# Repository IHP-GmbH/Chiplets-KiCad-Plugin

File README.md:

# Chiplets-KiCad-Plugin

KiCad (pcbnew) plugins for the IHP heterogeneous-integration ecosystem. This
repository hosts every current and future KiCad plugin built for chiplet and
interposer design on IHP SG13G2, so they share one license, one CI setup and
one place to look. Each plugin is self-contained under `plugins/<name>/` and is
installed independently.

Both plugins are alpha: `chiplet_export` lists what it does not verify in its
README's Status section, and `resizer_passive_elements` is a proof of concept.

## Plugins

| Plugin | What it does |
|--------|--------------|
| [`plugins/chiplet_export`](plugins/chiplet_export/README.md) | pcbnew action plugin that drives the HYP -> GDS -> canonical `.chiplet` pipeline in one click. Produces the canonical `.chiplet`, the interposer GDS, the driving Hyperlynx `.hyp`, and optionally a complete-assembly GDS. The same pipeline runs headless as `chiplet-export` ([reference](plugins/chiplet_export/CLI.md)). Consumed by adk-tools as a submodule. |
| [`plugins/resizer_passive_elements`](plugins/resizer_passive_elements/README.md) | pcbnew action plugin that resizes placed passive devices on the board. Today it covers `cap_cmim`: it regenerates each instance's footprint through the OpenIntM4TM2 `cmim_footprint_gen.py` from the `w`/`l` or `Capacitance` fields, then swaps it in preserving placement, nets and the technology fields the export flow reads. |

## Layout

```
Chiplets-KiCad-Plugin/
├── plugins/
│   ├── chiplet_export/       one self-contained pcbnew plugin (Python package)
│   │   ├── __init__.py       registers the ActionPlugin with pcbnew
│   │   ├── ...               action, dialog, pipeline/, writers/, tests/
│   │   ├── requirements.txt  that plugin's worker venv deps
│   │   └── README.md         that plugin's docs
│   └── resizer_passive_elements/   same shape, one plugin per directory
├── docs/                     pages adk-docs includes; docs/reference/ is generated
├── scripts/                  write_cli_help.py writes docs/reference/
├── .github/workflows/        CI, one matrix entry per plugin
├── pyproject.toml            test configuration for every plugin's suite
├── conftest.py               sibling checkouts for those suites
├── LICENSE                   GPL-3.0-or-later, applies repo-wide
└── README.md                 this file
```

Each plugin directory is a Python package in its own right: its `__init__.py`
registers the pcbnew action and its modules use relative imports, so the
package name is whatever the directory is called (`chiplet_export`). Nothing at
the repository root is a Python package; the root only carries shared metadata.

## Installing a plugin

Symlink (recommended for development) or copy the specific plugin directory,
not the whole repository, into KiCad's scripting plugins folder. For
`chiplet_export` on Linux with KiCad 9.0:

```bash
ln -s /path/to/Chiplets-KiCad-Plugin/plugins/chiplet_export \
      ~/.config/kicad/9.0/scripting/plugins/chiplet_export
```

Then follow that plugin's own README for its worker venv and dependencies
(`plugins/chiplet_export/README.md`).

## Adding a new plugin

1. Create `plugins/<new_name>/` with its own `__init__.py`, an `ActionPlugin`
   subclass that registers on import, a `README.md`, and a `tests/` suite. Use
   relative imports inside the package so it is loadable under `<new_name>`.
2. If it ships tests, give it a `requirements.txt`, add its requirements to
   the root `pyproject.toml` dependencies and its `tests` directory to
   `testpaths` there, and add `<new_name>` to the `matrix.plugin` list in
   `.github/workflows/tests.yml`. Every suite runs from the repository root
   under the one pytest configuration in `pyproject.toml`.
3. Keep the plugin self-contained: shared code, if it ever appears, is a
   separate decision, not an implicit dependency between plugin directories.

## License

GPL-3.0-or-later for the repository. See `LICENSE`. Individual plugins may
vendor code under compatible licenses and note it in their own README (for
example `chiplet_export` vendors a GPL-2.0-or-later Hyperlynx writer derived
from KiCad, redistributed under the "or later" clause).

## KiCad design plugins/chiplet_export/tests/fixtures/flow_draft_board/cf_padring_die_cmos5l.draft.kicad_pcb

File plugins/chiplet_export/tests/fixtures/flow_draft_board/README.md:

# flow_draft_board

One draft-path pair, the board and the sheet of the same run, for the
padring_die_cmos5l example: interposer_pnr's bumps, pdn, route, export and
schematic stages, with the interposer-pnr and gds_to_kicad that pair the draft
sheet with the draft board, run fresh in an ADK-Tools image on 2026-11-01 from
the elaborate outputs of the example's run of 2026-10-31. Route 38/38 nets with 0 DRC; `kicad-cli pcb drc
--schematic-parity` on the pair reports 0 issues.

`cf_padring_die_cmos5l.draft.kicad_pcb` is the draft board export wrote: three
die footprints (U1 to U3, `chiplet_dies:<top cell>`) and 32 wire-bond carrier
pads from `chiplet_carrier`, each with IO_PAD_ID its own Reference and linked
to no sheet symbol. It has no board-root property, and its `.kicad_pro` is not
kept here. Unchanged from the run; it names no host path. sha256:
`9eca915a4bbdaace4148dacd2968bab7d51490bd6b63304e09e3800e974fcc59`.

`cf_padring_die_cmos5l.draft.kicad_sch` is the system sheet the same run drew
(chiplet_to_kicad_sch), unchanged. Its title-block comment 1 holds the digest
of the run's `design.chiplet`. sha256:
`0bbf948c7161b148b46a9ad07959d492071d2ef00eebd769e3398ec668fddf8f`.

`test_board_save.py` saves copies of both the way a GUI save does;
`test_io_pad_ids.py` reads the board's carriers.

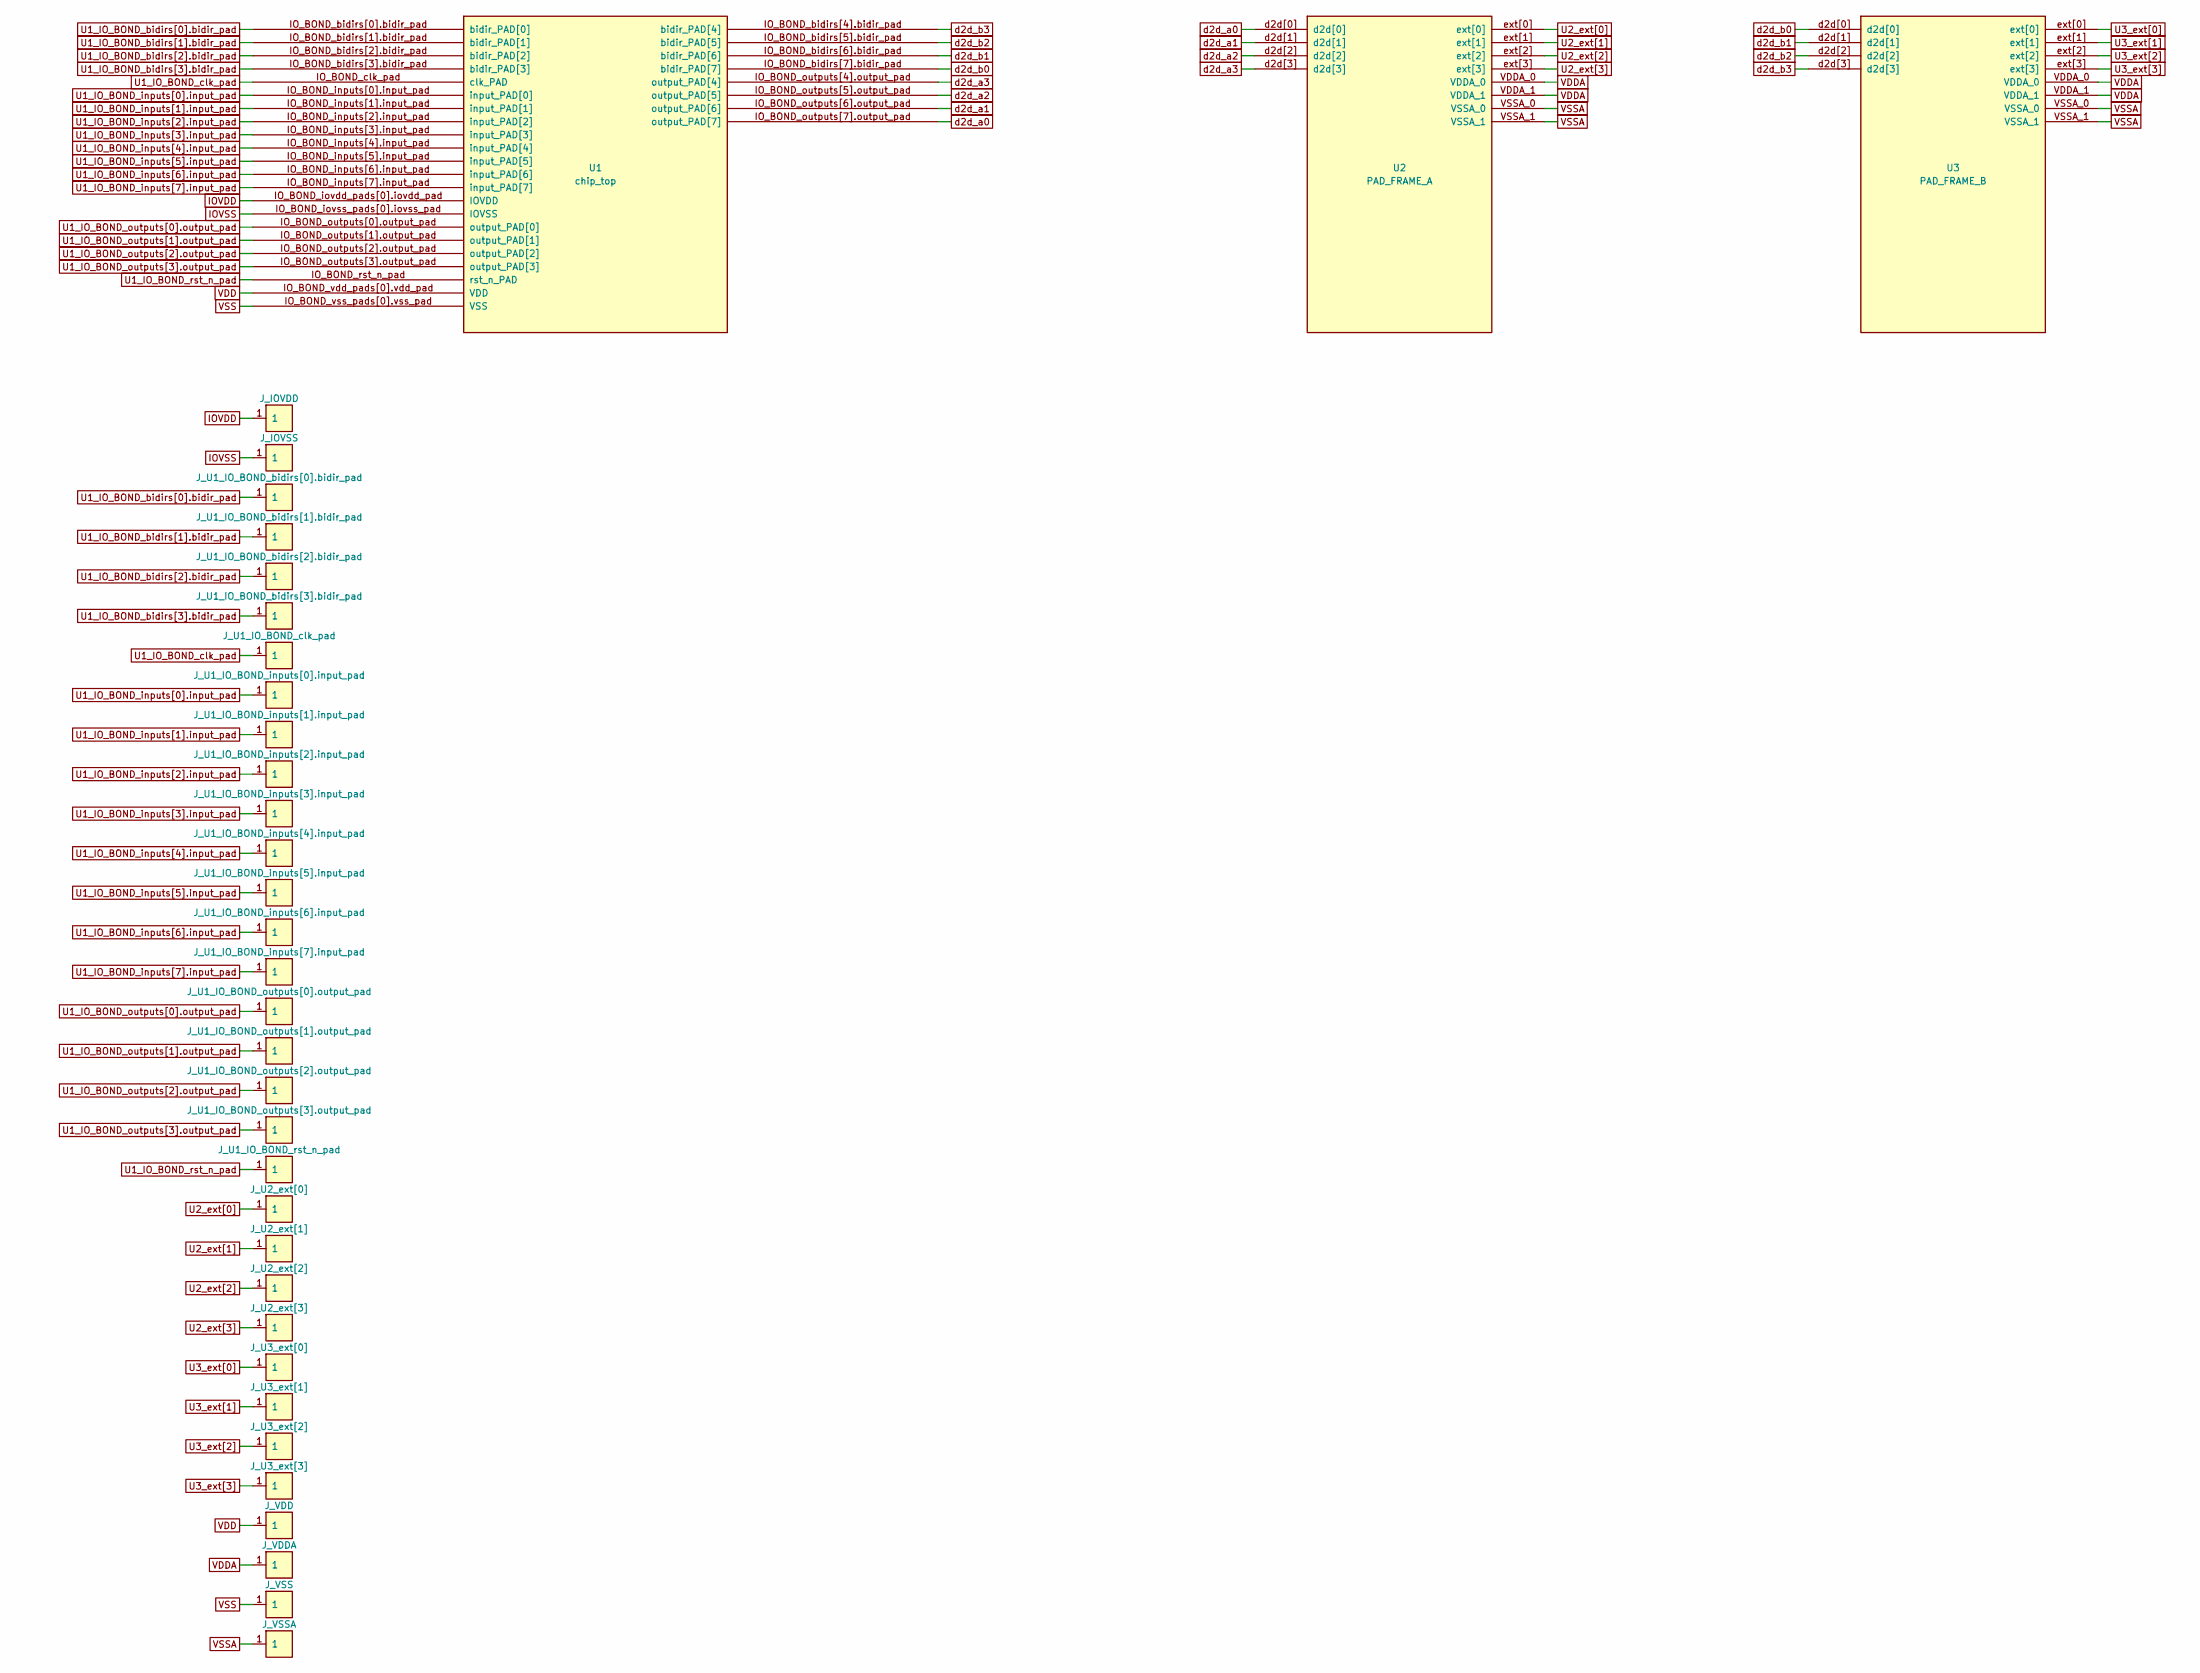
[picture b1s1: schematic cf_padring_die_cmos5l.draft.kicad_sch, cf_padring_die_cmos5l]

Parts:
J_IOVDD: EXT_PAD; EXT_PAD_80um
J_IOVSS: EXT_PAD; EXT_PAD_80um
J_U1_IO_BOND_bidirs[0].bidir_pad, J_U1_IO_BOND_bidirs[1].bidir_pad, J_U1_IO_BOND_bidirs[2].bidir_pad, J_U1_IO_BOND_bidirs[3].bidir_pad, J_U1_IO_BOND_clk_pad, J_U1_IO_BOND_inputs[0].input_pad, J_U1_IO_BOND_inputs[1].input_pad, J_U1_IO_BOND_inputs[2].input_pad, J_U1_IO_BOND_inputs[3].input_pad, J_U1_IO_BOND_inputs[4].input_pad, J_U1_IO_BOND_inputs[5].input_pad, J_U1_IO_BOND_inputs[6].input_pad, J_U1_IO_BOND_inputs[7].input_pad, J_U1_IO_BOND_outputs[0].output_pad, J_U1_IO_BOND_outputs[1].output_pad, J_U1_IO_BOND_outputs[2].output_pad, J_U1_IO_BOND_outputs[3].output_pad, J_U1_IO_BOND_rst_n_pad, J_U2_ext[0], J_U2_ext[1], J_U2_ext[2], J_U2_ext[3], J_U3_ext[0], J_U3_ext[1], J_U3_ext[2], J_U3_ext[3]: EXT_PAD; EXT_PAD_80um
J_VDD: EXT_PAD; EXT_PAD_80um
J_VDDA: EXT_PAD; EXT_PAD_80um
J_VSS: EXT_PAD; EXT_PAD_80um
J_VSSA: EXT_PAD; EXT_PAD_80um
U1: chip_top
U2: PAD_FRAME_A
U3: PAD_FRAME_B

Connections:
IOVDD: J_IOVDD.1, U1.IO_BOND_iovdd_pads[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 (IOVDD)
IOVSS: J_IOVSS.1, U1.IO_BOND_iovss_pads[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 (IOVSS)
U1_IO_BOND_bidirs[0].bidir_pad: J_U1_IO_BOND_bidirs[0].bidir_pad.1, U1.IO_BOND_bidirs[0].b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 (bidir_PAD[0])
U1_IO_BOND_bidirs[1].bidir_pad: J_U1_IO_BOND_bidirs[1].bidir_pad.1, U1.IO_BOND_bidirs[1].b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 (bidir_PAD[1])
U1_IO_BOND_bidirs[2].bidir_pad: J_U1_IO_BOND_bidirs[2].bidir_pad.1, U1.IO_BOND_bidirs[2].b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 (bidir_PAD[2])
U1_IO_BOND_bidirs[3].bidir_pad: J_U1_IO_BOND_bidirs[3].bidir_pad.1, U1.IO_BOND_bidirs[3].b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 (bidir_PAD[3])
U1_IO_BOND_clk_pad: J_U1_IO_BOND_clk_pad.1, U1.IO_BOND_clk_pad (clk_PAD)
U1_IO_BOND_inputs[0].input_pad: J_U1_IO_BOND_inputs[0].input_pad.1, U1.IO_BOND_inputs[0].i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 (input_PAD[0])
U1_IO_BOND_inputs[1].input_pad: J_U1_IO_BOND_inputs[1].input_pad.1, U1.IO_BOND_inputs[1].i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 (input_PAD[1])
U1_IO_BOND_inputs[2].input_pad: J_U1_IO_BOND_inputs[2].input_pad.1, U1.IO_BOND_inputs[2].i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 (input_PAD[2])
U1_IO_BOND_inputs[3].input_pad: J_U1_IO_BOND_inputs[3].input_pad.1, U1.IO_BOND_inputs[3].i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 (input_PAD[3])
U1_IO_BOND_inputs[4].input_pad: J_U1_IO_BOND_inputs[4].input_pad.1, U1.IO_BOND_inputs[4].i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 (input_PAD[4])
U1_IO_BOND_inputs[5].input_pad: J_U1_IO_BOND_inputs[5].input_pad.1, U1.IO_BOND_inputs[5].i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 (input_PAD[5])
U1_IO_BOND_inputs[6].input_pad: J_U1_IO_BOND_inputs[6].input_pad.1, U1.IO_BOND_inputs[6].i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 (input_PAD[6])
U1_IO_BOND_inputs[7].input_pad: J_U1_IO_BOND_inputs[7].input_pad.1, U1.IO_BOND_inputs[7].i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 (input_PAD[7])
U1_IO_BOND_outputs[0].output_pad: J_U1_IO_BOND_outputs[0].output_pad.1, U1.IO_BOND_outputs[0].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 (output_PAD[0])
U1_IO_BOND_outputs[1].output_pad: J_U1_IO_BOND_outputs[1].output_pad.1, U1.IO_BOND_outputs[1].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 (output_PAD[1])
U1_IO_BOND_outputs[2].output_pad: J_U1_IO_BOND_outputs[2].output_pad.1, U1.IO_BOND_outputs[2].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 (output_PAD[2])
U1_IO_BOND_outputs[3].output_pad: J_U1_IO_BOND_outputs[3].output_pad.1, U1.IO_BOND_outputs[3].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 (output_PAD[3])
U1_IO_BOND_rst_n_pad: J_U1_IO_BOND_rst_n_pad.1, U1.IO_BOND_rst_n_pad (rst_n_PAD)
U2_ext[0]: J_U2_ext[0].1, U2.ext[0]
U2_ext[1]: J_U2_ext[1].1, U2.ext[1]
U2_ext[2]: J_U2_ext[2].1, U2.ext[2]
U2_ext[3]: J_U2_ext[3].1, U2.ext[3]
U3_ext[0]: J_U3_ext[0].1, U3.ext[0]
U3_ext[1]: J_U3_ext[1].1, U3.ext[1]
U3_ext[2]: J_U3_ext[2].1, U3.ext[2]
U3_ext[3]: J_U3_ext[3].1, U3.ext[3]
VDD: J_VDD.1, U1.IO_BOND_vdd_pads[0]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 (VDD)
VDDA: J_VDDA.1, U2.VDDA_0, U2.VDDA_1, U3.VDDA_0, U3.VDDA_1
VSS: J_VSS.1, U1.IO_BOND_vss_pads[0]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 (VSS)
VSSA: J_VSSA.1, U2.VSSA_0, U2.VSSA_1, U3.VSSA_0, U3.VSSA_1
d2d_a0: U1.IO_BOND_outputs[7].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 (output_PAD[7]), U2.d2d[0]
d2d_a1: U1.IO_BOND_outputs[6].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 (output_PAD[6]), U2.d2d[1]
d2d_a2: U1.IO_BOND_outputs[5].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 (output_PAD[5]), U2.d2d[2]
d2d_a3: U1.IO_BOND_outputs[4].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 (output_PAD[4]), U2.d2d[3]
d2d_b0: U1.IO_BOND_bidirs[7].b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 (bidir_PAD[7]), U3.d2d[0]
d2d_b1: U1.IO_BOND_bidirs[6].b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 (bidir_PAD[6]), U3.d2d[1]
d2d_b2: U1.IO_BOND_bidirs[5].b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 (bidir_PAD[5]), U3.d2d[2]
d2d_b3: U1.IO_BOND_bidirs[4].b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 (bidir_PAD[4]), U3.d2d[3]

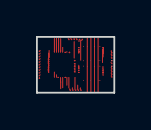
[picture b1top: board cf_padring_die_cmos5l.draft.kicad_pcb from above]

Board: 4 copper layers, 4.3 x 3.1 mm, 35 parts (0 on the bottom side), 40 nets.

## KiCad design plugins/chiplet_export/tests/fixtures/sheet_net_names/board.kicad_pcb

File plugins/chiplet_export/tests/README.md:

# Tests

This suite guards the HYP -> GDS -> canonical `.chiplet` pipeline against
regressions. The tricky part is that the tests have three different runtime
needs, so "just run pytest" only covers part of the suite.

- **Need `pcbnew`** (the writers that read a live `BOARD`): run from the
  Python bundled with KiCad, i.e. inside the `kicad-builder` Docker image.
  When `pcbnew` is missing, `pytest.importorskip("pcbnew")` skips those tests
  cleanly instead of failing. Files: `test_chiplet_writer.py`,
  `test_hyperlynx_writer.py`, `test_byte_exact_writers.py`,
  `test_cmim_extraction.py`, `test_io_pad_ids.py`. `test_board_save.py` (what a GUI save keeps of
  a flow board) runs its saves in a child process, so on a host it also runs
  with `KICAD_APPDIR` naming a KiCad AppDir. So does the last case of
  `test_plugin_registration.py` (both packages import beside KiCad's pcbnew
  without registering); its other cases use a stand-in pcbnew and run
  anywhere.
- **Need the `klayout.db` module** (GDS geometry generation), but not
  `pcbnew`: run on the host once the worker venv is on the path. They guard
  themselves with `pytest.importorskip("klayout.db")`. Files:
  `test_io_pads.py`, `test_via_geometry.py`, `test_boundary_annotations.py`,
  `test_cmim_devices.py`, `test_pillar_manifest.py` (the last two also need
  the sibling PDK checkouts), `test_die_outline_read.py`,
  `test_die_outline_finalize.py`, `test_die_layouts.py` and
  `test_attach_frame.py` (their worker runs use the vendored
  `fixtures/intm4tm2_reference.lyp` and read the mount plane from the
  fixture PDK root `fixtures/intm4tm2_pdk`, so they need no PDK).
- **Stdlib + pytest only**: run anywhere. Files: `test_discovery.py`,
  `test_runner.py`, `test_orchestrator.py`, `test_connection_stacks.py`,
  `test_layer_guard.py`, `test_hyp_to_gds_decoupling.py`,
  `test_yaml_escape.py`, `test_technology_id.py`,
  `test_die_outline_field.py` (two cases skip:
  the worker's side of the shared grammar without `klayout.db`, and the
  YAML read-back check without PyYAML).

Some of the host-runnable suites still skip themselves when sibling ecosystem
checkouts (the interconnect PDK, an SG13G2 PDK) are absent; they run
everywhere but may report skips rather than passes.

`conftest.py` puts the plugin package root (`plugins/chiplet_export`) on
`sys.path` so the absolute `chiplet_export.*` imports and the top-level
`import hyp_to_gds` resolve, and aliases that root as the `chiplet_export`
package in `sys.modules` when the directory has a different name. The plugin
dir is normally `chiplet_export` (also the KiCad symlink name), so the alias is
usually a no-op; it only matters for oddly named checkouts.

The finalizer reads the mount plane from the interposer PDK on every run, so
a test that finalizes a `.chiplet` points `INTERPOSER_PDK_ROOT` at
`fixtures/intm4tm2_pdk`, a root holding only a verbatim copy of the PDK's
stack descriptor (the `attach_frame_pdk` fixture in `conftest.py`, autouse in
the modules that finalize). The plane they see is then a known 10.8103, never
whichever PDK the host has, and they pass on a runner with none.

## Layout

| File | Coverage |
|------|----------|
| `test_chiplet_writer.py` (19) | Structural invariants on the YAML emitted by `writers/chiplet_writer.py`; includes the interf_u regression that exercises boards whose PROJECT wrapper lacks `GetTextVars`, the `CONNECTION`, `DIE_THICKNESS_UM` and `DIE_OUTLINE_LAYER` field round trips on a real board, two dies on project sheets (`<id>/layers.lyp`) written as two technologies named by their folders, and the stderr warning when two different sheets give one id. |
| `test_hyperlynx_writer.py` (7) | Structural invariants on the .hyp emitted by `writers/hyperlynx_writer.py` (metric headers, BOARD / STACKUP / DEVICES blocks, GDS_FILE propagation, PADSTACK id consistency). |
| `test_byte_exact_writers.py` (3) | Byte-exact diff: `write_chiplet` / `write_hyperlynx` output vs the C++ exporters `pcbnew.ExportBoardToChipletFile` / `ExportBoardToHyperlynxFile`. The third case synthesises a project that sets `INTERPOSER_ADAPTER` / `INTERCONNECT_ADAPTER`, which no committed fixture does, so the plain diff passed for the uninteresting reason that both sides read nothing. Those two are read from the project text variables and from nowhere else on both sides, and SWIG wrapped `PROJECT` in no KiCad version, so the Python lookup returned "" while the C++ exporter honoured them: the `.chiplet` silently lost its interposer adapter and its whole `interconnect:` block. Fixture discovery walks every ancestor's `examples/*/kicad/*.kicad_pcb`; the old single fixed path meant the whole parity guard skipped in the adk-tools image. |
| `test_discovery.py` (26) | Worker Python / hyp_to_gds.py discovery chain (env var, `.venv`, project text var read through `pcbnew.ExpandTextVars` since `PROJECT` is unwrapped, PATH probe with klayout+yaml import); the not-found message names `.venv`, `pip install -r requirements.txt` and which legs are actually probed; plus `preview_worker_python`, the probe-free variant the dialog shows as a hint (it must never spawn the import probe on the UI thread). |
| `test_runner.py` (12) | Async subprocess runner: line-by-line stdout/stderr callbacks, exit code propagation, cancel via `threading.Event`, a timeout, a child that never reads the caller's stdin, env/cwd plumbing. |
| `test_orchestrator.py` (229) | The pure helpers in `pipeline/orchestrator.py` that the dialog cannot exercise otherwise: `build_cli_args` (including the `--cmim-devices` passthrough), `build_adk_drc_argv`, `build_worker_env`, `load_interposer_adapter` / `load_interconnect_adapter`, `available_connection_types`, `connection_method_specs` + `format_connection_label` / `describe_connection_method` (the manifest-sourced dropdown labels; a method id must stay its label's prefix, and a missing manifest must degrade to bare ids rather than invent numbers), `describe_die_thickness_gaps`, `describe_interposer_body_default` (the interposer physical-body plausibility warning: the body now survives from the board stackup, so a value near the FR-4 default is flagged), `discover_dependency_root`, `discover_interposer_lyp`, `derive_interconnect_methods` + `write_ixn_methods_sidecar`, `_read_component_connections`, `describe_assembly_drc`, and `ExportOptions` / `ExportResult` DRC defaults (`discover_dependency_root` takes the worker's IntM4TM2 marker, and a set interposer root is shown as given, never replaced by the sibling, so the worker refuses a die PDK tree); and `--export-report` in `run_export`: the report is read once and the same names reach the preflight and both writers, an explicit io_pads sidecar is passed through unread, and a bad report or a refused carrier leaves no output directory; the connection-methods query stops on Cancel and on its timeout, and a Cancel during it stages nothing. |
| `test_connection_stacks.py` (9) | `writers/connection_stacks.py`: the manifest-driven connection-stack block must reproduce the literal the writer used to hardcode (and export_chiplet.cpp still emits), plus interconnect-id validation against the manifest. Skips without the interconnect PDK manifest. |
| `test_hyp_to_gds_decoupling.py` (82) | hyp_to_gds connection-stack tables decoupled from the interconnect PDK manifest: the manifest-sourced tables must reproduce the prior IHP literals exactly while the vendor demo method becomes selectable. Each method's landing is drawn by the pad cell of its fab anchor (CuPillarPad, SolderBumpPad) or refused before the GDS, every landing names its pad cell, an export checks each method once against one read of the manifest and draws its landings from that read, and a bump_mirror whose fab anchor API answers wrongly is a typed refusal (exit 5) for every method; the solder-bump export cases skip on an interposer PDK without SolderBumpPad. Skips without the manifest. An `INTERPOSER_PDK_ROOT` without the stack descriptor, a KLayout PDK tree that is not IntM4TM2 included, ends the run with `CARRIER_UNSUPPORTED_ROOT` from every reader (in the attach-frame cases too). |
| `test_io_pad_ids.py` (42) | Carrier pads read through interposer-pnr's shared `read_board_carriers`; each carrier reaches it as its reference, IO_PAD_ID, footprint library and sheet link, read off real boards. On a board drawn by export (a carrier from `chiplet_carrier` or carrying `IO_PAD_ID`), both carrier readers, the `.chiplet` writer and the io_pads sidecar, emit the io_pad id, per carrier even when two share a reference; a carrier without it, or two with one id, is refused by reference as a `CarrierIdError`, a carrier left out of the BOM included, and with every id lost the readers never fall back to the `J<n>` designators. A hand-drawn board (another library, no symbol links) keeps its references. A board drawn by export whose carriers link sheet symbols needs its report; one drawn by hand from its own sheet (a project library, linked) does not; a draft updated from its draft sheet reads by its own report. Net names on a real `export --form` board and report (`fixtures/sheet_net_names`): both outputs carry the planner's names, a sheet-only net is unbound; a version 6 report names carrier nets as its version 3 twin, with or without a feature this copy does not know, and one without the `sheet` feature follows no sheet; a report written for other carrier references (a draft's on a sheet board, a sheet board's on a draft) or pairing a carrier with another io_pad, a sheet's report on a board no carrier of which is linked, and a carrier net in neither map are refused by both writers with nothing written; only report refusals are `BoardReportError`; a die's sheet path alone needs no report; a board drawn against no sheet keeps each carrier's own net, the same bytes with no report and with one that follows no sheet. |
| `test_draft_net_names.py` (12) | `draft_net_names.read_export_report`, stdlib only: a real report read through the vendored interposer-pnr reader maps sheet names back to the planner's, no path is no report, a report of a board that follows no sheet has no names, version 5 names as 3 and 4 as 2 (reserved copper names no net), a 5 or a 4 with no `reserved`, a 3 with one, a 6 that lists no features and a newer version are refused, and every refusal (no file, not JSON, not an export report, a bad round_trip) names the file. The rules themselves are tested in interposer-pnr. |
| `test_io_pads.py` (6) | I/O pad geometry in `hyp_to_gds.GDSGenerator.add_io_pads` (TopMetal2 squares, `io_class` dispatch that skips `flipped_bump` / `tsv_bump`, invalid-size skip, missing file) plus `update_chiplet_file` io_pads injection and layout-ref relativization. |
| `test_cmim_devices.py` (40) | Worker side of the `cap_cmim` path: the w/l unit contract (a `um`/`u` suffix means micrometres, a bare number means metres, and every convention must land on the same plate), sidecar loading, IntM4TM2 `cmim` PCell placement (plate centred on the footprint position, origin snapped to `techParams.grid`), unplaceable devices reported to the caller rather than skipped, no empty group cell left behind, and the regression that SG13G2 via PCells survive the intm4tm2 technology rebind (with `db.Cell` handles in the via cache, `write()` died in `Cell.flatten`). A plate the PCell would refuse never reaches it: the PCell does not return None on bad parameters, it hands back a nameless empty cell that the GDS writer emits as an empty STRNAME record, which makes the whole file unreadable, and a plate large enough to pass its own coercion sends its O(w*l) via loop into an unbounded allocation. Skips without the interposer PDK. |
| `test_cmim_extraction.py` (13) | Board side of the same path: `is_cmim` on both the `Model` and `Sim.Name` spelling, `write_cmim_devices_json` normalising every field convention to `w_um`/`l_um` in the io_pads frame (micrometres, Y negated), unusable footprints skipped with no file written, the orientation recorded for the GDS frame, refs of footprints that could not be described handed back to the caller (the worker's own guard cannot see those), and a round trip of the exporter's own sidecar back through the worker's reader. |
| `test_via_geometry.py` (15) | SG13G2 via PCell bootstrap (must come up when a PDK and PCell deps are present; a silent rectangle fallback is a regression) and the JSON-honoring `_create_simple_via` rectangle fallback that reads `PDK_VIA_PARAMS`. The cut count in integer dbu: a pad equal to the k x k landing gives k and one dbu more gives k+1 (k = 1, 3, 10, METRIC and ENGLISH); a 3x3 landing draws 9 cuts and a dieless HYP of 1.9 um one-cut vias draws one cut per via, on the PCell path and the rectangle fallback alike. Skips without an SG13G2 PDK. |
| `test_die_outline_read.py` (44) | The die outline read in `die_outline_gds.py` on synthetic GDS: one merged rectangle under the one top cell (found through child cells, abutting pieces merged), and a named refusal for two shapes, corner-touching boxes, a non-rectangle, a ring, zero width, an absent layer, texts only, a missing, unreadable or directory path, several top cells, and a dbu other than the assembly's 0.001 um. Width and height are exact Decimal products on both axes and off the origin (123457 DBU is 123.457, not the float 123.45700000000001); each file is opened once per run whatever path names it, and causes name the resolved file; the flag parsers name the bad token. |
| `test_die_outline_finalize.py` (52) | The finalizer with `--die-outline-layers` / `--die-outline-exempt`: declared dies sized exactly from the outline (two layers of one file, a symlinked file, a `${VAR}` path), exempt dies keep their size and are logged, every refusal (undeclared, both, not a die, no flags, duplicate refs, missing, unreadable or wrong-dbu GDS for exempt dies too) raised before the `.chiplet` is touched and all offenders named at once. A die an `--io-pads` entry replaces needs no flag, and a shared HYP ref nothing uses is left alone. Worker runs: the boundary manifest polygon is where the outline lands in the complete GDS (face-up and flip-chip, at right angles and at 45 degrees), an exempt die keeps the cell bbox, the same holds without a `.chiplet`, the head reads the HYP `GDS_FILE` once, a device at another dbu or a die that cannot be placed leaves no complete GDS, and a refused CLI run leaves a pre-populated output directory byte-identical. |
| `test_die_layouts.py` (53) | `--die-layouts`: the sidecar read into exact 0.001 um database units, and a named refusal (`match=`) for every malformed file or entry (not JSON, not an object, NaN, a missing, unknown or repeated key, a relative, unexpanded, missing or directory layout, an empty top cell, a box that is not four numbers, not whole database units or not a box, a die named twice, an empty reference), all offenders at once. The finalizer writes the full layout relative and uncopied, the contract's top cell and exactly the two metadata keys, and without the flag writes the bytes it wrote before; it refuses, leaving the `.chiplet` untouched, a reference that is no die (absent, the interposer, an `--io-pads` pad), a full layout at another dbu, without the contract cell or with it under another cell, and a box that matches one file only (naming both files and boxes). Worker runs: the boundary and both GDS (dates aside) equal a run without the flag, the complete GDS composes the abstract, and a refused run leaves the tree byte-identical. Also the argv, the CLI's absolute path and exit 2, and the `.hyp` and the worker's argv under `run_export` with the flag and without. |
| `test_cli_reference.py` (7) | `CLI.md` against the `chiplet-export` parser: every flag has a row and every row names a flag, a required flag says `required`, a switch says `flag`/`off`, choices and string defaults appear in their cells, and the exit table has exactly the tool's four codes. `--help` (which names `CLI.md`) and a usage error run with pcbnew unimportable; the plugin README links the reference before its first section. |
| `test_attach_frame.py` (31) | The mount plane read from the interposer PDK's `beol.attachment_surface_z_um`: the value as written and its source; a named refusal (`match=`, naming `INTERPOSER_PDK_ROOT` and the key) without the PDK, for a descriptor that is not JSON, and for a key that is missing or not a finite number (a string, a bool, null, a list, NaN, Infinity); each z the exact decimal sum of the plane and the heights as written (five-decimal heights keep them; no float tail). The finalizer writes the plane and that z, refuses without the PDK leaving the `.chiplet` untouched, and takes a number a direct caller gives. Worker runs name the plane read, and a root without the descriptor leaves the tree byte-identical; without a `.chiplet` no plane is read. |
| `test_system_technology_overlay.py` (31) | `--system-chiplet` on the draft and System pair of a reference flow run of the two-die bondpad example (`fixtures/two_die_bondpad`): each component takes the technology of the System component with its id and `technologies` is the System's entries for exactly those ids, copied as written; without the flag the output is byte for byte `finalized.chiplet`, which the finalizer made before the flag existed. Every refusal (no System component, two of them, no technology, an undeclared id, a relative `layer_properties` or `stackup`, an entry that is not a mapping) names the id with `match=` and leaves the `.chiplet` untouched, all offenders at once; a System die the draft lacks and an `--io-pads` component are not errors. Worker runs write the ids, and a refused or unreadable System leaves the tree byte-identical. Also the argv without the flag, the CLI's absolute path and its exit 2 on a missing file. |
| `test_die_outline_field.py` (154) | The `DIE_OUTLINE_LAYER` footprint field (`die_outline.py`) against strict pcbnew doubles whose graphics, courtyard and bounding box raise when read: the `LAYER/DATATYPE` grammar (the worker parses with the very same objects), which footprints are read (dies sized from their GDS) and which never are (marked dies, IO pads, `cap_cmim`, BOM-excluded), one role per reference for the dialog's rows, and one refusal naming every offender, each cause once (no field, empty, malformed, no `GDS_FILE` with the BOM hint, a reference two dies share or a die shares with an IO pad or a `.hyp` device, a reference the flags, the `.hyp` or the `.chiplet` would change, checked against PyYAML itself, a partial or misdirected explicit map). Through `run_export`: the refusal comes before any output directory, workspace or writer, even for a board whose first die is fine; the argv carries the preflight's map and the exempt list derived from the markers, in both worker modes, and nothing when the worker reads no outlines; the CLI creates nothing on a refusal. Also `write_die_outline_layers` against field doubles, the real `write_chiplet` loop emitting exactly the dies the preflight names, and the regeneration driver's `--use-existing-hyp` path deriving both flags and refusing before it writes anything. |
| `test_boundary_annotations.py` (14) | The opt-in, viewer-only boundary annotation layer in hyp_to_gds: off by default, one polygon + one label per boundary when on, never the legacy 190/0 fab layer, the boundary manifest left untouched, and an annotation layer on any landing pad fab layer refused. |
| `test_layer_guard.py` (3) | Loud guard for unmapped board layers: fails the conversion when more than `UNMAPPED_FAIL_FRACTION` of trace elements sit on unmapped layers, tolerates stray layers below the threshold with one aggregate warning. |
| `test_pillar_manifest.py` (8) | The `<stem>.pillars.json` pillar manifest (schema `adk-pillar-manifest` 1.0.0): written on bump-path runs (empty `pillars` array when nothing is placed, nothing at all without the bump path), positions equal to the drawn GDS instances rebased into the canonical GDS-bbox-corner frame (the `.chiplet` frame), including auto-resolved bumps flagged `moved_by_auto_resolve`, per-die method/diameter, deterministic sorted output. Skips without the sibling PDK checkouts. |
| `test_seal_ring.py` (42) | `--seal-ring`: the PCell placed on a rectangular outline and carried into the complete GDS; each refusal (no outline, two loops, not a rectangle, under the minimum, no library or PCell, an empty cell, 39/4 off the outline) writes nothing; keep-outs clipped to 39/4; the stop for geometry in the ring band or within the space rule, passing at the rule and stopping one grid step closer; the boundary sidecar digest taken after the fill; the fill engine taken only from the resolved PDK root. The logic runs on a fake PCell library, so no PDK is needed; the real PCell cases (the ring on the outline, the minimum, a CMIM placed before the ring surviving its second technology bind) skip without one, as does the check that the clearance layers are the sealring deck's SEAL.REQ.4 layers plus Passiv. Flag off: argv and GDS bytes (timestamps zeroed) pinned to the export from before the flag. |
| `test_technology_id.py` (20) | The technology id a die's `LYP_FILE` gives (`writers/_technology.py`): the file stem for a sheet named after its technology, so today's ids do not move, and the holding folder for a project's per-technology `layers.lyp`; a `layers.lyp` with no folder above it (bare, `./`, right under a `${VAR}`) keeps `layers`, and no other name reads the folder. |
| `test_yaml_escape.py` (18) | The shared YAML scalar escaper (`writers/_yaml.py`): bare-vs-quoted classifier, escape set, and round-trips through a YAML parser (guards the C++/Python byte-locked pair at its most divergence-prone boundary). |
| `regenerate_wirebond_demo.py` | Driver script (not a pytest module): regenerates the wire-bond demo `.chiplet` through the Python pipeline; output feeds the chiplet-studio `CoordFrameContract*` gtests. Its `--use-existing-hyp` path derives `--die-outline-layers` / `--die-outline-exempt` from the board the way `run_export` does. |
| `check_complete_gds_alignment.py` | klayout regression script (not a pytest module): asserts U1's flipped cell sits over the cu-pillar array in the complete-assembly GDS. |

201 test functions across the 14 `test_*.py` files. A handful skip on hosts
without the KiCad fixtures (interf_u demo, wire-bond demo `.kicad_pcb`) or
without sibling PDK checkouts; the worker venv is expected at `.venv` (see
`requirements.txt`: `klayout>=0.28`, `PyYAML>=6.0`).

## Running

Host-runnable tests (no Docker). The stdlib-only suites run as-is; the
klayout-only suites need the worker venv's `klayout.db`, so run them through
`.venv/bin/python`:

```bash
cd plugins/chiplet_export
.venv/bin/python -m pytest \
    tests/test_discovery.py \
    tests/test_runner.py \
    tests/test_orchestrator.py \
    tests/test_connection_stacks.py \
    tests/test_layer_guard.py \
    tests/test_hyp_to_gds_decoupling.py \
    tests/test_yaml_escape.py \
    tests/test_technology_id.py \
    tests/test_io_pads.py \
    tests/test_via_geometry.py \
    tests/test_boundary_annotations.py \
    tests/test_cmim_devices.py \
    tests/test_pillar_manifest.py -v
```

Some of these skip when the interconnect/SG13G2 PDK siblings are absent; that
is expected on a lone checkout.

The pytest configuration is the repository root's `pyproject.toml`, found from
here or from the root. A bare run deselects the cases that start the klayout
application (`klayout_binary`); `-m klayout_binary` runs them. The cases that
read a sibling checkout carry `needs_sibling_sources`, and find it through the
variable that names it, `$HCDP_ROOT/<id>`, or the walk from this checkout, in
that order (the root `conftest.py`).

Byte-exact diff only (requires kicad-builder + reference files):

```bash
docker run --rm \
  -v $PWD/..:$PWD/.. \
  kicad-builder bash -c "
    cd $PWD &&
    PYTHONPATH=/tmp/pytest_lib pip install --target /tmp/pytest_lib pytest pyyaml &&
    PYTHONPATH=/tmp/pytest_lib:$PYTHONPATH \
        python3 -m pytest tests/test_byte_exact_writers.py -v
  "
```

Full suite from inside the kicad-builder Docker image:

```bash
ROOT=/path/to/checkouts   # kicad/ and chiplet_kicad_plugin/ side by side
docker run --rm \
  -v $ROOT:$ROOT \
  -e LD_LIBRARY_PATH=$ROOT/kicad/build/release/common:$ROOT/kicad/build/release/common/gal:$ROOT/kicad/build/release/pcbnew:$ROOT/kicad/build/release/api:$ROOT/kicad/build/release/pcbnew/python:$ROOT/kicad/build/release/3d-viewer/3d_cache/sg \
  -e PYTHONPATH=$ROOT/kicad/build/release/pcbnew/python:/tmp/pytest_lib \
  kicad-builder bash -c "
    pip install --target /tmp/pytest_lib pytest pyyaml &&
    cd $ROOT/chiplet_kicad_plugin/plugins/chiplet_export &&
    python3 -m pytest tests/ -v --ignore=tests/regenerate_wirebond_demo.py \
                                --ignore=tests/check_complete_gds_alignment.py
  "
```

The two `--ignore`d files are driver scripts, not pytest modules.

Round-trip regression net (driver script + chiplet-studio gtests):

```bash
# 1. Regenerate the wire-bond demo .chiplet via the Python pipeline.
#    Reuse the same LD_LIBRARY_PATH / PYTHONPATH as the full-suite block above.
#    The demo board ships a closed Edge.Cuts outline, so the full end-to-end
#    path (Hyperlynx writer -> hyp_to_gds.py) runs directly; --use-existing-hyp
#    stays available for boards still authored without an outline.
docker run --rm -v $ROOT:$ROOT -e LD_LIBRARY_PATH=... -e PYTHONPATH=... \
  kicad-builder \
  $ROOT/chiplet_kicad_plugin/plugins/chiplet_export/.venv/bin/python \
  $ROOT/chiplet_kicad_plugin/plugins/chiplet_export/tests/regenerate_wirebond_demo.py \
      --board $ROOT/adk-tools/examples/interposer_wire_bonding_demo/kicad/interposer_wire_bonding_demo.kicad_pcb \
      --connection cupillar_opt1 \
      --output-dir $ROOT/_tmp_regen

# 2. Feed the regenerated .chiplet to the chiplet-studio gtests.
cd $ROOT/chiplet-studio/build && ./tests/chiplet_tests \
    --gtest_filter='CoordFrameContract*'
```

`regenerate_wirebond_demo.py` defaults `--board` to the bundled
`examples/interposer_wire_bonding_demo/kicad/` board (resolved next to the
plugin) and also accepts `--lyp`, `--io-pads`, `--connection`, and
`--allow-drc-fail`. Its default mode exits like `chiplet-export`: 3 when the
files were written but the assembly DRC did not pass (a container without
the ADK reads NOT RUN, so pass `--allow-drc-fail` there), 0 only when it
passed. `--require-drc` is still accepted and changes nothing.
`--use-existing-hyp` runs no DRC and exits 0 when the worker does. Every
unmarked die on the board needs its
`DIE_OUTLINE_LAYER` field (plugin README, *Per-die settings*); either path
refuses a board without one before it writes anything.

Optional fixture override (point at any board, e.g. a chiplet
project under development):

```bash
export CHIPLET_WRITER_BOARD=/path/to/board.kicad_pcb
export HYPERLYNX_WRITER_BOARD=/path/to/board.kicad_pcb  # may be the same
```

## GUI smoke tests (wxPython) — deferred, for the Docker image team

The PLUG-16 source-authority regression tests distinguish selected roots from
automatic discovery. Nonblank option, environment and project selections remain
authoritative even when incomplete; an automatic checkout without an actual
manifest file is ignored. Pure resolver/preflight cases label their reader
doubles. Two separate subprocess probes use unchanged production PDK reader
bytes to check that the worker environment pins A despite a competing B; they
explicitly skip if that reader source is unavailable. They do not run the full
layout worker or prove process-wide absence of every possible PDK installation.
The no-PDK orchestration test uses writer/worker doubles and checks the warning
in the callback, durable run log and output manifest. This mode omits connection
stacks and manifest-backed interconnect method validation; export completion is
not an interconnect-verification claim.

The `ChipletExportDialog` in `dialog_chiplet_export.py` (the pcbnew action-plugin
dialog) has focused control-double coverage in `test_dialog_catalogue.py` for
typed source refusal during construction and refresh, atomic catalogue updates,
recovery, visible no-PDK warnings, and synchronous Run preflight before option
collection or board writes. The per-die outline-layer column is covered the
same way: the board's field text is shown raw (a malformed value is not
erased), exempt and non-die rows say what they are, a board the column cannot
read keeps its rows and says so, and Run turns an empty or malformed row, or a
preflight refusal, into one message box with no field write-back and no
export, or writes the rows back after the CONNECTION and thickness fields.
The worker's method availability is asked once per worker and root pair, a
stale answer is dropped, and each answer is logged once, held while the
catalogue is refused.
These tests execute the real dialog methods with a narrowly scoped wx import
shim; they do not construct native widgets or validate sizers. Other logic is
covered indirectly by the pure
helpers in `pipeline/orchestrator.py` and `pipeline/discovery.py`
(`connection_method_specs`, `format_connection_label`,
`describe_connection_method`, `describe_die_thickness_gaps`,
`describe_interposer_body_default`, `preview_worker_python`, ...), but the wx
plumbing itself — sizers, the removal of the "Canonical .chiplet" checkbox, the
per-die grid, the connection-combo labels, the worker-python hint row, the
`SetSizeHints` minimum width — still needs dedicated visual assertions.

`test_dialog_catalogue_wx.py` adds four native-widget smoke cases: construct a
real dialog on a fresh `pcbnew.BOARD` with a selected data-only manifest and no
reader; recover through the real refresh callback using a labelled reader
double; recover from a candidate-inspection permission error during construction;
and refuse a Run click before the root-change debounce without board writes or
export. It checks editable source controls and an enabled Close
button, and destroys the dialog and stops its timer without entering a modal
loop. Deferred window deletions are drained before the fixture destroys its
owned wx application. The standalone bootstrap temporarily suppresses KiCad
action registration during the initial package import because no KiCad
application registry exists in that process. It restores registration immediately,
verifies that the imported package belongs to this checkout, then starts pytest.
Production registration is unchanged and is not covered by this smoke. Direct
pytest in a capable environment can register the parent package before any
test-module guard executes, so use the bootstrap for this standalone run.
The recovery double tests GUI lifecycle, not supported-reader conformance.
On hosts missing wx, pcbnew, or a Linux display, this file reports an explicit
skip. In a capable image, run from the repository root:

```bash
xvfb-run -a python3 scripts/run_dialog_catalogue_wx.py -vv -s
```

Acceptance requires all four selected cases to run and the process to exit 0;
skips, passing assertions followed by a shutdown crash, and timeout termination
are not native GUI acceptance. The bootstrap preserves pytest's exit code and
normal interpreter shutdown. This smoke does not replace the broader visual
checks below.

This needs a **wxPython + display** environment, which the host worker venv
(`.venv`) does not have. It is handed to the team that builds/tests the Docker
images because the pieces already live there:

- **`import wx` works in `kicad-builder` today** (wxPython **4.2.1** is in the
  image). Only a virtual display is missing for constructing widgets.
- **Level 1 — import smoke (runs green in `kicad-builder` right now).** Catches
  import/syntax/symbol-wiring breakage without any display. Proven recipe:

  ```bash
  ROOT=/path/to/checkouts   # kicad/ and chiplet_kicad_plugin/ side by side
  docker run --rm -v $ROOT:$ROOT \
    -e LD_LIBRARY_PATH=$ROOT/kicad/build/release/common:$ROOT/kicad/build/release/common/gal:$ROOT/kicad/build/release/pcbnew:$ROOT/kicad/build/release/api:$ROOT/kicad/build/release/pcbnew/python:$ROOT/kicad/build/release/3d-viewer/3d_cache/sg \
    -e PYTHONPATH=$ROOT/chiplet_kicad_plugin/plugins:$ROOT/kicad/build/release/pcbnew:$ROOT/kicad/build/release/pcbnew/python \
    kicad-builder python3 -c "import wx, pcbnew; import chiplet_export.dialog_chiplet_export as d; assert hasattr(d, 'ChipletExportDialog')"
  ```

  Note: the dialog uses a **relative** import (`from .pipeline.orchestrator
  import ...`), so it must be imported as `chiplet_export.dialog_chiplet_export`
  with `$ROOT/chiplet_kicad_plugin/plugins` (the parent of the plugin package)
  on `PYTHONPATH`, **not** as a top-level `import dialog_chiplet_export`. This
  historical import-only recipe does not establish safe standalone lifecycle:
  `action_plugin.cpp ... assert "PgmOrNull()" failed` indicates attempted
  registration without the KiCad application host. Use the bootstrap above for
  the native dialog smoke; that assertion is not accepted as benign evidence.

- **Level 2 — headless construct smoke (needs one addition to the image).**
  `kicad-builder` has **no `xvfb`** (`xvfb-run` is absent), so a `wx.App` +
  `ChipletExportDialog(...)` cannot be constructed. The action item for the
  Docker team is to add `xvfb` (`apt-get install -y xvfb`) to the image, then run
  the construction under `xvfb-run -a python3 ...`, load the wire-bond demo board
  (`kicad_designs/interposer_wire_bonding_demo/...`) via `pcbnew.LoadBoard`,
  construct `ChipletExportDialog`, and assert the UX invariants from the dialog
  cleanup: no "Canonical .chiplet" checkbox (`_cb_chiplet` gone), the connection
  combo labels carry PDK specs (id stays the label prefix), the per-die grid has
  header cells, the worker-python hint row is present, and the dialog's minimum
  width did not grow versus a baseline.

Until the image gains `xvfb`, wire Level 1 into the Docker test flow as-is — it
is a real, green build-gate on the dialog today.

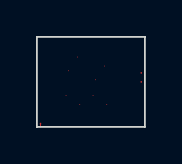
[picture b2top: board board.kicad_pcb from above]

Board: 4 copper layers, 6.0 x 5.0 mm, 7 parts (0 on the bottom side), 2 nets.

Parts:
D_FLIP: CELL_D_FLIP
D_FR: CELL_D_FR
D_ROT: CELL_D_ROT
D_UP: CELL_D_UP
J1, J2, J10: EXT_PAD_80um

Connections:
OUT: D_UP.A0, J1.1
vss: D_FLIP.A1, J2.1, J10.1

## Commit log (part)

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2026-05-12 chore: initial chiplet_kicad_plugin skeleton
    KiCad pcbnew action plugin for the single-button chiplet export
    workflow. Registers a pcbnew.ActionPlugin under
    Tools > External Plugins > Chiplet Export; the dialog and writers
    are placeholders until later gates.
    Structure
    chiplet_export_action.py ActionPlugin subclass + Run() entry
2026-05-12 feat: port export_chiplet.cpp to writers/chiplet_writer.py
    write_chiplet(board, output_path) replicates the intermediate
    .chiplet emission performed today by kicad/pcbnew/exporters/
    export_chiplet.cpp, using the pcbnew SWIG bindings. The output
    keeps the _metadata.finalize_required: true marker; the
    canonical .chiplet is produced downstream by
    hyp_to_gds.py --update-chiplet-file.
2026-05-12 feat: wire dialog, orchestrator and ActionPlugin for chiplet export
    Implements Gate 47.6 of TaskList #47. The plugin is now end-to-end
    functional in pcbnew: a single Run produces a canonical .chiplet plus
    the requested GDS artifacts.
    pipeline/orchestrator.py
    - ExportOptions dataclass: output_dir, three output toggles
    (canonical .chiplet, interposer GDS, complete-assembly GDS), keep
2026-05-22 fix: iterate hyperlynx nets by name to match C++ exporter byte order
    The previous implementation walked board.GetNetsByNetcode() and
    sorted by integer netcode. The C++ exporter (export_hyperlynx.cpp
    line 630) iterates m_board->GetNetInfo() instead, which dispatches
    through NETINFO_LIST::iterator -> m_netNames (a std::map<wxString,
    NETINFO_ITEM*>) and therefore emits nets in alphabetic order by
    NET NAME.
2026-05-22 test: gate 47.7e — chiplet-studio regression net green via plugin pipeline
    Add tests/regenerate_wirebond_demo.py: a headless driver that
    regenerates the wire-bond demo end-to-end through the plugin
    pipeline (writers + hyp_to_gds.py worker) so the chiplet-studio
    gtest battery can be re-run against output produced by the plugin
    instead of the legacy C++ menu actions.
    Result of running CoordFrameContractSynth.* + CoordFrameContract-
2026-05-22 fix: surface writer exceptions instead of hanging the dialog
    When a Python writer raised inside the worker thread, the exception
    propagated out of run_export, killed the worker, and the dialog was
    left in 'Running ...' with no error in the log because the on_done
    callback only fired when run_export returned normally.
    Two layers of defense:
    * orchestrator.run_export wraps the write_hyperlynx and write_chiplet
2026-05-22 test: gate 47.7f - chiplet-studio visual smoke green
    Regenerated interposer_wire_bonding_demo via the Python plugin pipeline
    (write_hyperlynx -> write_chiplet -> hyp_to_gds.py with --lyp, --io-pads,
    and --cupillar-gds) and loaded the resulting .chiplet in the
    chiplet-studio container. Visual checks:
    - Scene loads without warnings.
    - Interposer carries the merged cu-pillar geometry.
2026-05-22 docs: tests README update for iter 1 closure
    - Table now reflects all current test modules: byte-exact diff
    (47.7b), the GetTextVars regression (47.7d fix #63), the cupillar
    passthrough (47.7f), and the regenerate-script driver (47.7e).
    - End-of-iter-1 totals spelled out so future contributors know what
    green looks like.
    - Running section: split stdlib-only, byte-exact-only, full-suite,
2026-05-26 fix: embed interposer_ihp.lyp so hyp_to_gds.py default path works
    Bug surfaced by gate 47.9 headless smoke against the interf_u demo:
    hyp_to_gds.py defaults --lyp to Path(__file__).parent /
    'interposer_ihp.lyp', but the iter 1 plugin only copied the script
    without the layer-properties file. Result: smoke exits 1 with
    'Error: Could not find .../chiplet_kicad_plugin/interposer_ihp.lyp'
    and the interposer GDS is never written.
2026-05-31 hyp_to_gds: read exchange0 layer from ADK config
2026-06-01 plugin: emit boundary manifest from hyp_to_gds, drop exchange0 190/0 stamp
    hyp_to_gds stamped each placed chiplet's mechanical boundary on exchange0
    (190/0), a real IHP SG13G2 fab layer, and resolved that number through a
    silent fallback that could drift from the ADK config.
    Record each boundary instead and write a <stem>.boundaries.json manifest
    beside the GDS (per-chiplet instance/source-die/transform + polygon in DBU
    and um). The ADK assembly DRC auto-discovers it; no boundary lands in any
2026-06-03 decouple connection_stacks from hardcode; add interconnect.adapter axis
    The .chiplet connection_stacks block is now sourced from the interconnect PDK
    manifest (single source of truth) instead of a hardcoded table, via the pure
    writers/connection_stacks.py (host-testable, byte-identical to the prior literal
    so the C++ parity gate stays green). The writer also emits an optional
    interconnect: block mirroring interposer:, driven by the INTERCONNECT_ADAPTER
    text var. The orchestrator reads interconnect.adapter from the .chiplet (default
2026-06-03 Remove 3D interconnect body layers from interposer .lyp copy
    Drop the cu-pillar/solder-bump property blocks (500/35, 501/35, 502/36)
    from the plugin's interposer_ihp.lyp; these bodies are owned by the
    interconnect PDK (interconnect.lyp). Keeps the plugin copy in sync with
    the interposer PDK.
2026-06-03 Adopt plain intm4tm2 interposer naming
    DEFAULT_INTERPOSER_ADAPTER and the chiplet writer's adapter fallback
    follow the plain formal product id (intm4tm2, no vendor prefix). The
    interposer technology id emitted in .chiplet files changes from the
    generic interposer_tech to intm4tm2 so downstream stackup resolution
    keys on the product name alone. Bundled layer properties renamed to
    intm4tm2.lyp. Byte-exact lockstep with the C++ exporter.
2026-06-04 Harden interposer PDK discovery; fail loud when pillars are required
    Cu-pillar generation resolves bump_mirror via the ecosystem discovery
    convention (INTERPOSER_PDK_ROOT, then an upward walk) instead of fixed
    relative arithmetic, and a missing interposer PDK is now a hard error
    when a connection stack was requested: a complete GDS without its
    pillars looks fabricable and no downstream DRC can flag the absent
    geometry. Discovery covered by tests.
2026-06-04 Make PDK roots explicit, visible inputs of the export dialog
    The dialog used to resolve the interposer PDK, interconnect PDK and ADK
    silently through the discovery chain -- workable while the ecosystem has
    exactly one of each, but not a scalable shape for the tool. The three
    roots are now first-class dialog fields: pre-filled with the discovered
    checkout (provenance at a glance), editable to point the export at any
    other checkout. An override travels to the worker subprocesses as the
2026-06-04 Derive per-method interconnect sidecar for the assembly DRC
    The orchestrator reads the .chiplet's per-die connections (hand-rolled
    parser, sibling of the adapter-block reader -- KiCad's Python has no
    PyYAML), groups dies per interconnect method, takes each method's
    pitch/spacing from the interconnect PDK manifest, and writes
    <gds-stem>.ixn_methods.json next to the complete GDS (sibling of the
    boundaries manifest). build_adk_drc_argv gains a trailing
2026-06-05 Discovery walk accepts upstream repository dir names as aliases
    The sibling walk only matched the canonical ecosystem names (interposer,
    interconnect_pdk, adk, gds_to_kicad), so default GitHub clone dirs
    (OpenIntM4TM2, IHP-Interconnect-IntM4TM2, ADK, gds-to-kicad) resolved
    nothing and setups had to rename checkouts. Walk tables now carry both
    names, canonical first. Env-first behaviour unchanged.
2026-06-05 Style CONNECTION write-back: hidden, F.Fab, small text
    SetField alone creates the field with KiCad's defaults (visible on
    F.SilkS at 1.27 mm), which drew the method ids as giant text across the
    um-scale board. Restyle on every write so previously affected boards
    self-heal on their next export.
2026-06-07 hyp_to_gds: real SG13G2 via_stack PCells + JSON-honoring fallback
    Self-register the SG13_dev PCell library under plain python: discover
    the PDK (PDK_ROOT env, then sibling IHP-Open-PDK walk), register the
    sg13g2 technology, import sg13g2_pycell_lib and bind the layout to the
    technology (the library is tech-bound; lookup returns None otherwise).
    Previously the PCell path only worked inside a KLayout session, so
    every containerized/CLI run silently used the rectangle fallback.
2026-06-10 Point boundary-manifest writer at the adk schema doc
    One-line comment in _write_boundary_manifest referencing
    adk/docs/boundary_manifest.md: the adk readers now exact-match the
    manifest version, so producers and readers must bump together.
2026-06-10 Pre-fill the dialog's interposer LYP picker with the discovered default
    An empty picker invited selecting the wrong .lyp (the interconnect one
    carries only bump aux layers, so the layer guard rejects every trace).
    New discover_interposer_lyp() mirrors the worker default: INTERPOSER_LYP
    env -> project text variable -> canonical tech/intm4tm2.lyp under the
    discovered interposer PDK root -> bundled copy. The dialog now shows the
    file the run will actually use; clearing the field still falls back to
2026-06-20 writers: restore byte-exact parity with the C++ exporters
    Three latent divergences the single-PDK / 2-layer fixtures never trigger:
    - chiplet technologies block emitted in dict insertion order; the C++
    techMap is a std::map (sorted), so multi-PDK assemblies diverged. Sort by id.
    - hyperlynx PADSTACK copper layers emitted in CuStack order instead of the
    C++ outLayers.Seq() raw-bit order; boards with inner copper diverged. Use .Seq().
    - INTERPOSER_ADAPTER / INTERCONNECT_ADAPTER read via _lookup_property
2026-06-20 hyp_to_gds/discovery: robustness and honest diagnostics
    - parse() emits a descriptive error (naming the file) on malformed HYP data
    instead of a raw ValueError traceback. (F9)
    - add_io_pads skips a malformed sidecar (bad JSON, non-object, non-numeric
    size/position) with a warning instead of crashing. (F10)
    - main() refuses a --boundary-viz-layer that collides with a fab layer
    (189/0, 190/0, cu-pillar fab); the painter clears that layer first. (F11)
2026-06-20 plugin: dead code, doc/comment accuracy, and SPDX hygiene
    - Remove the dead add_segment() (no callers; carried a stray DEBUG print);
    add_segments_as_paths is the live trace path. (F16)
    - Correct the misleading 'Deprecated' note on --pad-locations, which is the
    active auto cu-pillar generation path. (F42)
    - README: I/O pads and cu-pillars are auto-extracted / headless-only, not
    dialog pickers; fix the cu-pillar troubleshooting step. (F41)
2026-06-21 chiplet_writer: mirror assembly.name fallback and interposer tech guard
    Mirror the export_chiplet.cpp fixes so the byte-locked writer stays
    consistent: non-empty assembly.name fallback and the interposer-collision
    disambiguation. No-ops on clean input; the byte-parity gate stays green.
2026-06-21 writers: fix yaml_scalar trailing-newline divergence + boundary tests
    Adversarial review of the escaping diff found the Python bare-scalar regex
    anchored with $ (not \Z). Python's $ matches before a trailing newline, so
    a value ending in '\n' (a reachable footprint reference) was emitted BARE
    with a raw newline, diverging from the byte-locked C++ yamlScalar (which
    quotes and escapes it) and injecting a newline into the .chiplet. Anchor
    with \Z so the predicate matches the C++ byte loop.
